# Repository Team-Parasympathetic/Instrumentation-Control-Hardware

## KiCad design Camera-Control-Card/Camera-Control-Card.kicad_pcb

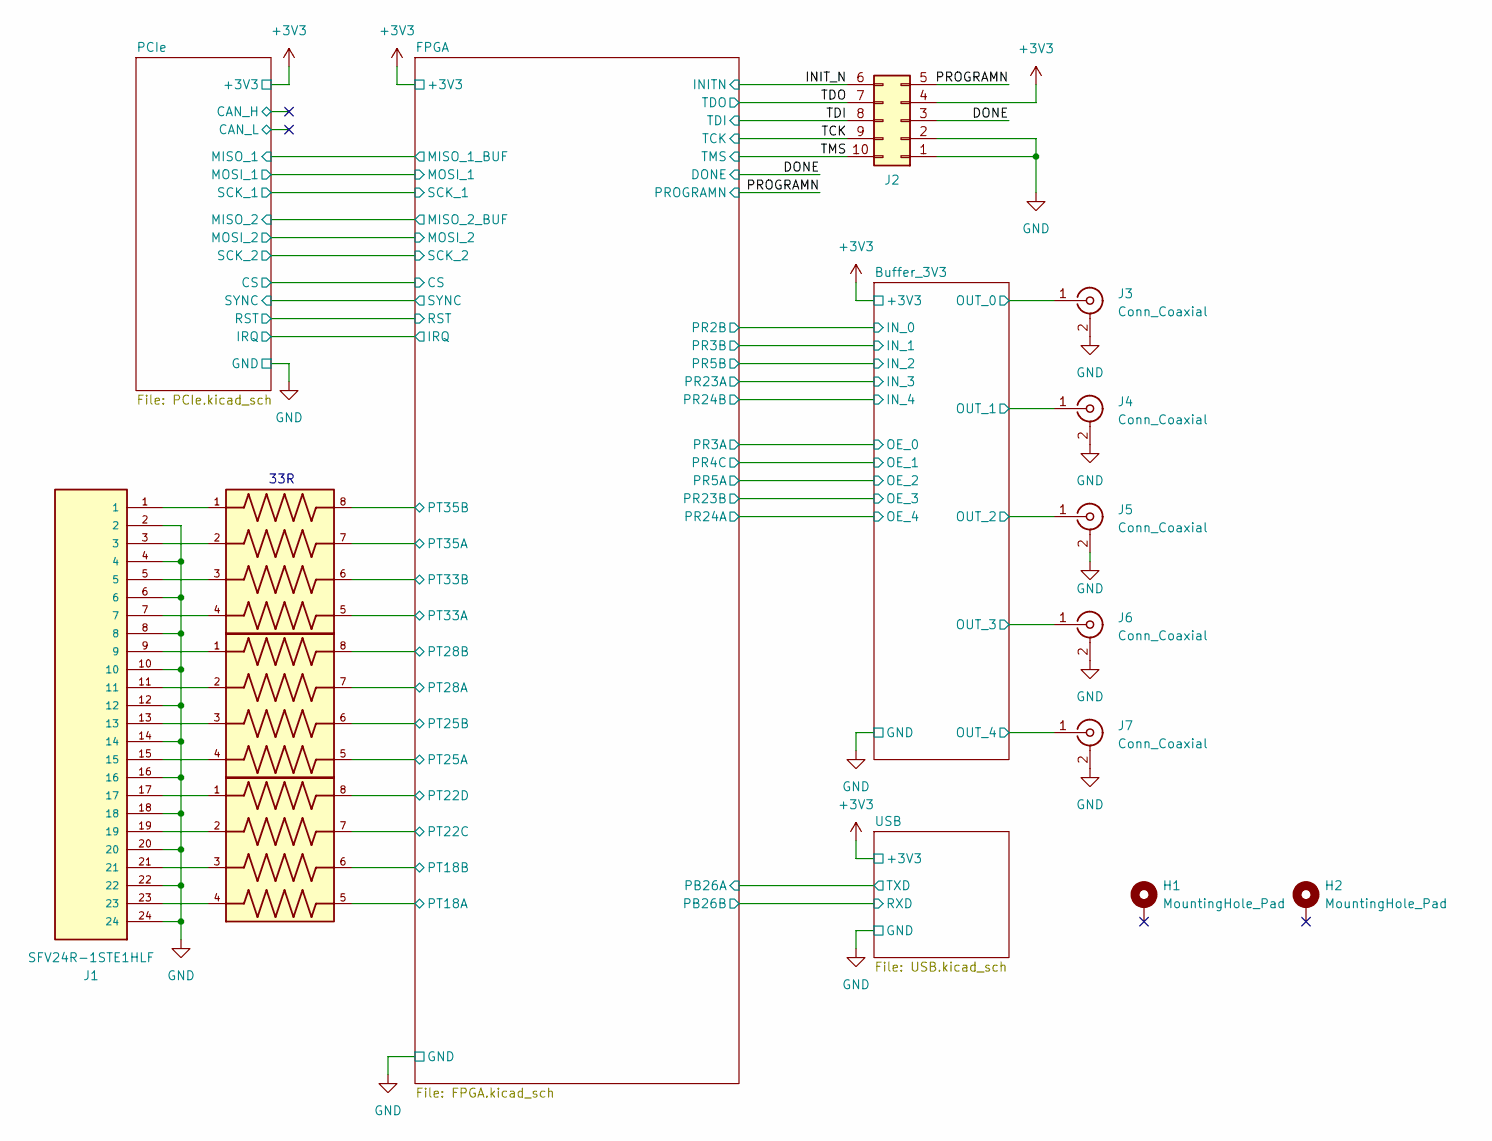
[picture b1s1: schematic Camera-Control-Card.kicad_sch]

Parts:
H1, H2: MountingHole_Pad; MountingHole_2.2mm_M2_DIN965_Pad_TopBottom
J1: SFV24R-1STE1HLF; AMPHENOL_SFV24R-1STE1HLF; PARTREV C
J2: Conn_02x05_Counter_Clockwise; AMPHENOL_78207-110HLF
J3, J4, J5, J6, J7: Conn_Coaxial; SMA_Molex_73251-1153_EdgeMount_Horizontal
RN1, RN2, RN3: EXB-38V330JV; RESCAXS80P320X160X60-8N

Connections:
+3V3: J2.4; also elsewhere on the board
/Buffer_3V3/OUT_0: J3.1 (In); also elsewhere on the board
/Buffer_3V3/OUT_1: J4.1 (In); also elsewhere on the board
/Buffer_3V3/OUT_2: J5.1 (In); also elsewhere on the board
/Buffer_3V3/OUT_3: J6.1 (In); also elsewhere on the board
/Buffer_3V3/OUT_4: J7.1 (In); also elsewhere on the board
/DONE: J2.3; also elsewhere on the board
/FPGA/PT18A: RN3.5; also elsewhere on the board
/FPGA/PT18B: RN3.6; also elsewhere on the board
/FPGA/PT22C: RN3.7; also elsewhere on the board
/FPGA/PT22D: RN3.8; also elsewhere on the board
/FPGA/PT25A: RN2.5; also elsewhere on the board
/FPGA/PT25B: RN2.6; also elsewhere on the board
/FPGA/PT28A: RN2.7; also elsewhere on the board
/FPGA/PT28B: RN2.8; also elsewhere on the board
/FPGA/PT33A: RN1.5; also elsewhere on the board
/FPGA/PT33B: RN1.6; also elsewhere on the board
/FPGA/PT35A: RN1.7; also elsewhere on the board
/FPGA/PT35B: RN1.8; also elsewhere on the board
/INIT_N: J2.6; also elsewhere on the board
/PROGRAMN: J2.5; also elsewhere on the board
/TCK: J2.9; also elsewhere on the board
/TDI: J2.8; also elsewhere on the board
/TDO: J2.7; also elsewhere on the board
/TMS: J2.10; also elsewhere on the board
GND: J1.2, J1.4, J1.6, J1.8, J1.10, J1.12, J1.14, J1.16, J1.18, J1.20, J1.22, J1.24, J2.1, J2.2, J3.2 (Ext), J4.2 (Ext), J5.2 (Ext), J6.2 (Ext), J7.2 (Ext); also elsewhere on the board
unnamed: J1.1, RN1.1
unnamed: J1.3, RN1.2
unnamed: J1.5, RN1.3
unnamed: J1.7, RN1.4
unnamed: J1.9, RN2.1
unnamed: J1.11, RN2.2
unnamed: J1.13, RN2.3
unnamed: J1.15, RN2.4
unnamed: J1.17, RN3.1
unnamed: J1.19, RN3.2
unnamed: J1.21, RN3.3
unnamed: J1.23, RN3.4

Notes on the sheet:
33R

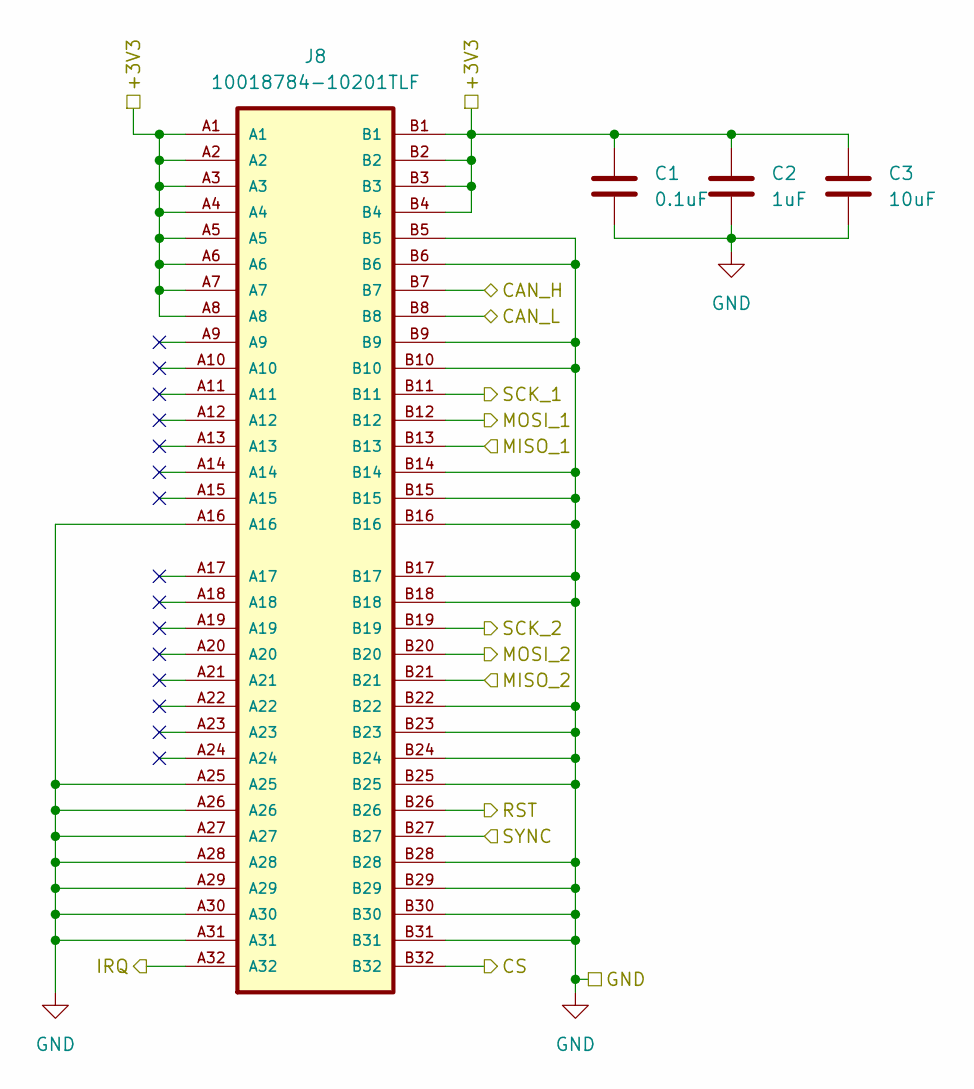
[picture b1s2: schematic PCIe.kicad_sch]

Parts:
C1: 0.1uF; C_0805_2012Metric
C2: 1uF; C_0805_2012Metric
C3: 10uF; CP_Elec_6.3x5.9
J8: 10018784-10201TLF; BUS_PCIexpress_x4; PARTREV A

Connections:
+3V3: C1.1, C2.1, C3.1, J8.A1, J8.A2, J8.A3, J8.A4, J8.A5, J8.A6, J8.A7, J8.A8, J8.B1, J8.B2, J8.B3, J8.B4; also elsewhere on the board
/FPGA/CS: J8.B32; also elsewhere on the board
/FPGA/IRQ: J8.A32; also elsewhere on the board
/FPGA/MISO_1_BUF: J8.B13; also elsewhere on the board
/FPGA/MISO_2_BUF: J8.B21; also elsewhere on the board
/FPGA/MOSI_1: J8.B12; also elsewhere on the board
/FPGA/MOSI_2: J8.B20; also elsewhere on the board
/FPGA/RST: J8.B26; also elsewhere on the board
/FPGA/SCK_1: J8.B11; also elsewhere on the board
/FPGA/SCK_2: J8.B19; also elsewhere on the board
/FPGA/SYNC: J8.B27; also elsewhere on the board
/PCIe/CAN_H: J8.B7
/PCIe/CAN_L: J8.B8
GND: C1.2, C2.2, C3.2, J8.A16, J8.A25, J8.A26, J8.A27, J8.A28, J8.A29, J8.A30, J8.A31, J8.B5, J8.B6, J8.B9, J8.B10, J8.B14, J8.B15, J8.B16, J8.B17, J8.B18, J8.B22, J8.B23, J8.B24, J8.B25, J8.B28, J8.B29, J8.B30, J8.B31; also elsewhere on the board

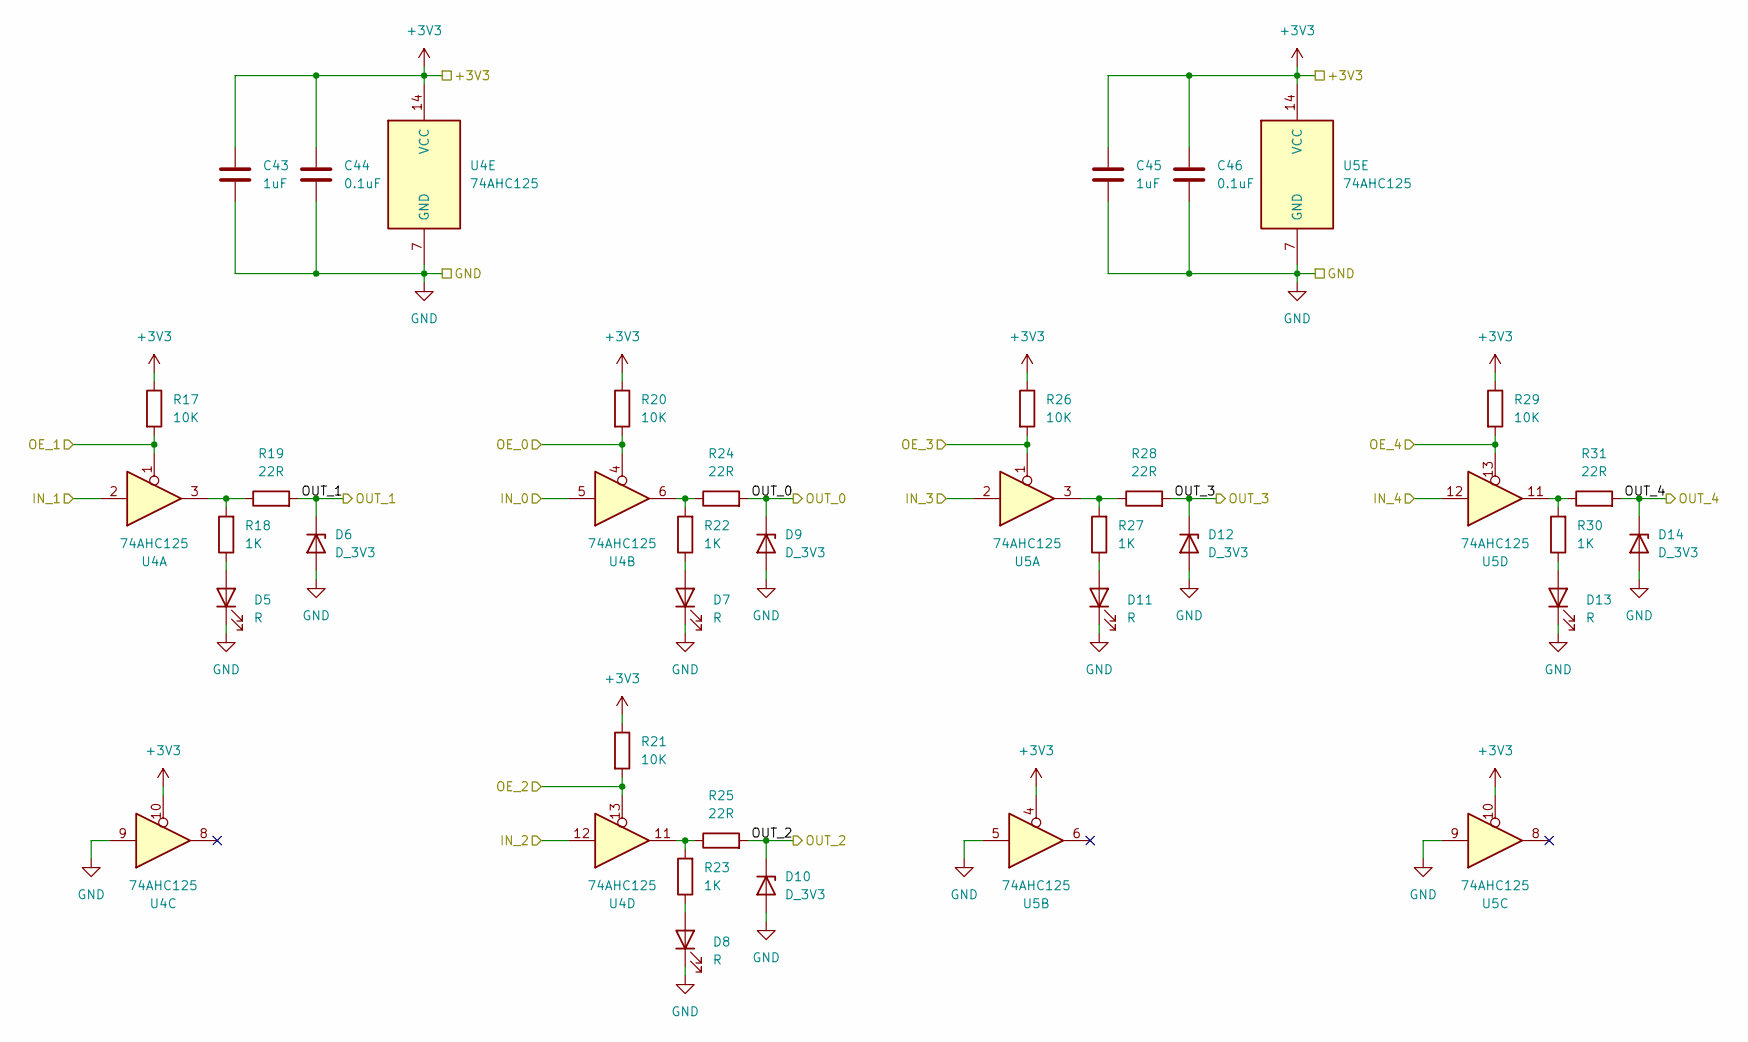
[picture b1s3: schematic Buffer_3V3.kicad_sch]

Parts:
C43, C45: 1uF; C_0603_1608Metric
C44, C46: 0.1uF; C_0603_1608Metric
D5, D7, D8, D11, D13: R; LED_0603_1608Metric
D6, D9, D10, D12, D14: D_3V3; D_SOD-323
R17, R20, R21, R26, R29: 10K; R_0603_1608Metric
R18, R22, R23, R27, R30: 1K; R_0603_1608Metric
R19, R24, R25, R28, R31: 22R; R_0603_1608Metric
U4, U5: 74AHC125; TSSOP-14_4.4x5mm_P0.65mm

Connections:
+3V3: C43.1, C44.1, C45.1, C46.1, R17.1, R20.1, R21.1, R26.1, R29.1, U4.10, U4.14 (VCC), U5.4, U5.10, U5.14 (VCC); also elsewhere on the board
/Buffer_3V3/IN_0: U4.5; also elsewhere on the board
/Buffer_3V3/IN_1: U4.2; also elsewhere on the board
/Buffer_3V3/IN_2: U4.12; also elsewhere on the board
/Buffer_3V3/IN_3: U5.2; also elsewhere on the board
/Buffer_3V3/IN_4: U5.12; also elsewhere on the board
/Buffer_3V3/OE_0: R20.2, U4.4; also elsewhere on the board
/Buffer_3V3/OE_1: R17.2, U4.1; also elsewhere on the board
/Buffer_3V3/OE_2: R21.2, U4.13; also elsewhere on the board
/Buffer_3V3/OE_3: R26.2, U5.1; also elsewhere on the board
/Buffer_3V3/OE_4: R29.2, U5.13; also elsewhere on the board
/Buffer_3V3/OUT_0: D9.1 (K), R24.2; also elsewhere on the board
/Buffer_3V3/OUT_1: D6.1 (K), R19.2; also elsewhere on the board
/Buffer_3V3/OUT_2: D10.1 (K), R25.2; also elsewhere on the board
/Buffer_3V3/OUT_3: D12.1 (K), R28.2; also elsewhere on the board
/Buffer_3V3/OUT_4: D14.1 (K), R31.2; also elsewhere on the board
GND: C43.2, C44.2, C45.2, C46.2, D5.1 (K), D6.2 (A), D7.1 (K), D8.1 (K), D9.2 (A), D10.2 (A), D11.1 (K), D12.2 (A), D13.1 (K), D14.2 (A), U4.7 (GND), U4.9, U5.5, U5.7 (GND), U5.9; also elsewhere on the board
unnamed: D5.2 (A), R18.1
unnamed: D7.2 (A), R22.1
unnamed: D8.2 (A), R23.1
unnamed: D11.2 (A), R27.1
unnamed: D13.2 (A), R30.1
unnamed: R18.2, R19.1, U4.3
unnamed: R22.2, R24.1, U4.6
unnamed: R23.2, R25.1, U4.11
unnamed: R27.2, R28.1, U5.3
unnamed: R30.2, R31.1, U5.11

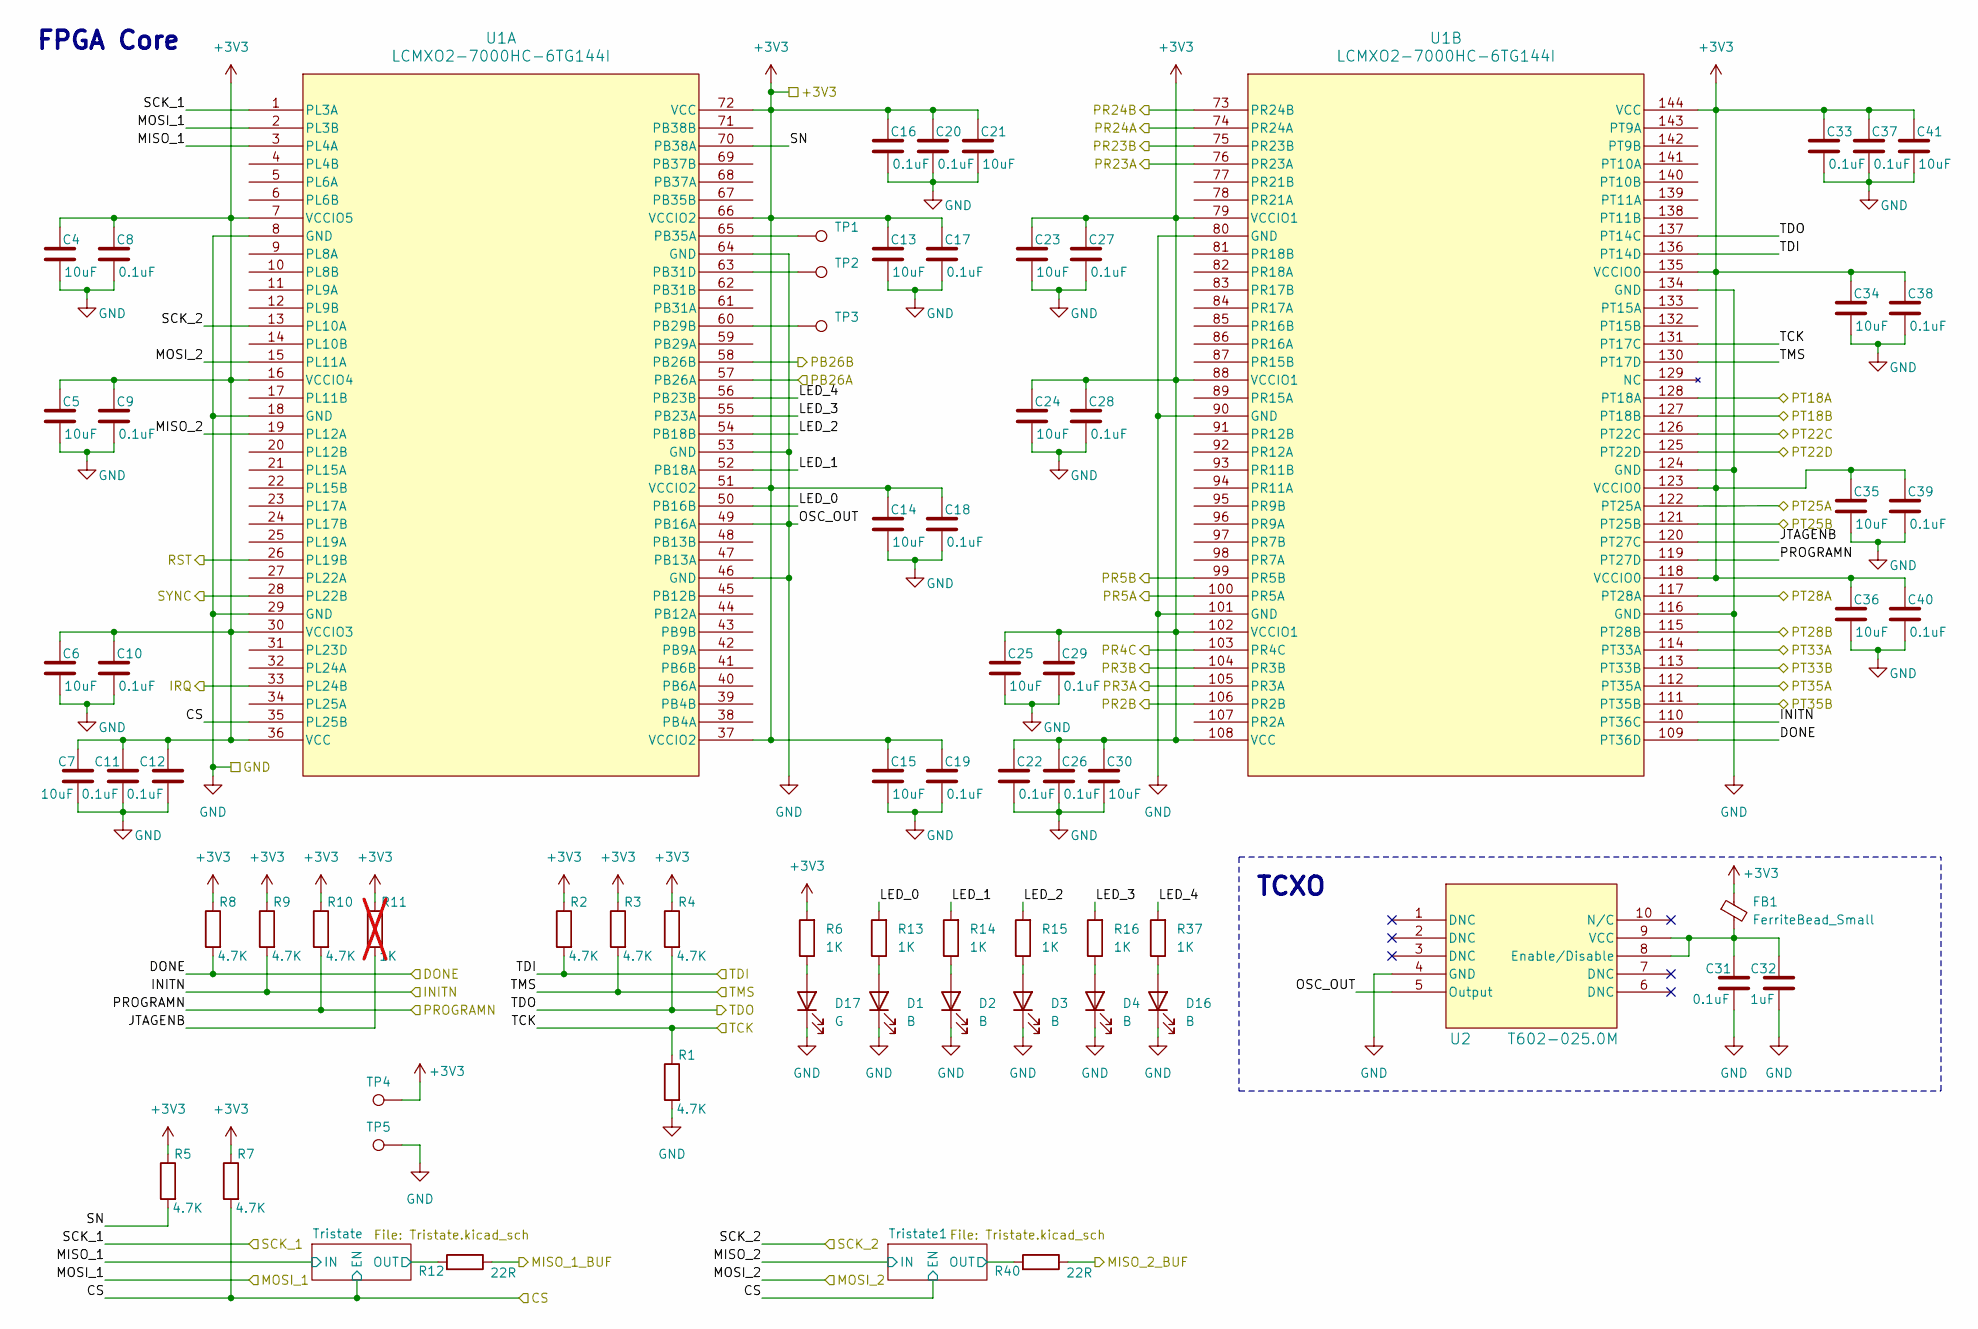
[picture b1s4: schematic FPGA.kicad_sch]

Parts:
C4, C5, C6, C7, C13, C14, C15, C21, C23, C24, C25, C30, C34, C35, C36, C41: 10uF; C_0603_1608Metric
C8, C9, C10, C11, C12, C16, C17, C18, C19, C20, C22, C26, C27, C28, C29, C31, C33, C37, C38, C39, C40: 0.1uF; C_0603_1608Metric
C32: 1uF; C_0603_1608Metric
D1, D2, D3, D4, D16: B; LED_0603_1608Metric
D17: G; LED_0603_1608Metric
FB1: FerriteBead_Small; L_0805_2012Metric
R1, R2, R3, R4, R5, R7, R8, R9, R10: 4.7K; R_0603_1608Metric
R6, R13, R14, R15, R16, R37: 1K; R_0603_1608Metric
R11: 1K; R_0603_1608Metric; not fitted
R12, R40: 22R; R_0603_1608Metric
TP1, TP2, TP3, TP4, TP5: TestPoint; TestPoint_Pad_D1.0mm
U1: LCMXO2-7000HC-6TG144I; TQFP144_LAT
U2: T602-025.0M; T602-025.0M_CNW

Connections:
+3V3: C4.1, C5.1, C6.1, C7.1, C8.1, C9.1, C10.1, C11.1, C12.1, C13.1, C14.1, C15.1, C16.1, C17.1, C18.1, C19.1, C20.1, C21.1, C22.1, C23.1, C24.1, C25.1, C26.1, C27.1, C28.1, C29.1, C30.1, C33.1, C34.1, C35.1, C36.1, C37.1, C38.1, C39.1, C40.1, C41.1, FB1.1, R2.1, R3.1, R4.1, R5.1, R6.2, R7.1, R8.1, R9.1, R10.1, R11.1, TP4.1, U1.7 (VCCIO5), U1.16 (VCCIO4), U1.30 (VCCIO3), U1.36 (VCC), U1.37 (VCCIO2), U1.51 (VCCIO2), U1.66 (VCCIO2), U1.72 (VCC), U1.79 (VCCIO1), U1.88 (VCCIO1), U1.102 (VCCIO1), U1.108 (VCC), U1.118 (VCCIO0), U1.123 (VCCIO0), U1.135 (VCCIO0), U1.144 (VCC); also elsewhere on the board
/Buffer_3V3/IN_0: U1.106 (PR2B); also elsewhere on the board
/Buffer_3V3/IN_1: U1.104 (PR3B); also elsewhere on the board
/Buffer_3V3/IN_2: U1.99 (PR5B); also elsewhere on the board
/Buffer_3V3/IN_3: U1.76 (PR23A); also elsewhere on the board
/Buffer_3V3/IN_4: U1.73 (PR24B); also elsewhere on the board
/Buffer_3V3/OE_0: U1.105 (PR3A); also elsewhere on the board
/Buffer_3V3/OE_1: U1.103 (PR4C); also elsewhere on the board
/Buffer_3V3/OE_2: U1.100 (PR5A); also elsewhere on the board
/Buffer_3V3/OE_3: U1.75 (PR23B); also elsewhere on the board
/Buffer_3V3/OE_4: U1.74 (PR24A); also elsewhere on the board
/DONE: R8.2, U1.109 (PT36D); also elsewhere on the board
/FPGA/CS: R7.2, U1.35 (PL25B); also elsewhere on the board
/FPGA/IRQ: U1.33 (PL24B); also elsewhere on the board
/FPGA/JTAGENB: R11.2, U1.120 (PT27C)
/FPGA/LED_0: R13.2, U1.50 (PB16B)
/FPGA/LED_1: R14.2, U1.52 (PB18A)
/FPGA/LED_2: R15.2, U1.54 (PB18B)
/FPGA/LED_3: R16.2, U1.55 (PB23A)
/FPGA/LED_4: R37.2, U1.56 (PB23B)
/FPGA/MISO_1: U1.3 (PL4A); also elsewhere on the board
/FPGA/MISO_1_BUF: R12.1; also elsewhere on the board
/FPGA/MISO_2: U1.19 (PL12A); also elsewhere on the board
/FPGA/MISO_2_BUF: R40.1; also elsewhere on the board
/FPGA/MOSI_1: U1.2 (PL3B); also elsewhere on the board
/FPGA/MOSI_2: U1.15 (PL11A); also elsewhere on the board
/FPGA/PB26A: U1.57 (PB26A); also elsewhere on the board
/FPGA/PB26B: U1.58 (PB26B); also elsewhere on the board
/FPGA/PT18A: U1.128 (PT18A); also elsewhere on the board
/FPGA/PT18B: U1.127 (PT18B); also elsewhere on the board
/FPGA/PT22C: U1.126 (PT22C); also elsewhere on the board
/FPGA/PT22D: U1.125 (PT22D); also elsewhere on the board
/FPGA/PT25A: U1.122 (PT25A); also elsewhere on the board
/FPGA/PT25B: U1.121 (PT25B); also elsewhere on the board
/FPGA/PT28A: U1.117 (PT28A); also elsewhere on the board
/FPGA/PT28B: U1.115 (PT28B); also elsewhere on the board
/FPGA/PT33A: U1.114 (PT33A); also elsewhere on the board
/FPGA/PT33B: U1.113 (PT33B); also elsewhere on the board
/FPGA/PT35A: U1.112 (PT35A); also elsewhere on the board
/FPGA/PT35B: U1.111 (PT35B); also elsewhere on the board
/FPGA/RST: U1.26 (PL19B); also elsewhere on the board
/FPGA/SCK_1: U1.1 (PL3A); also elsewhere on the board
/FPGA/SCK_2: U1.13 (PL10A); also elsewhere on the board
/FPGA/SN: R5.2, U1.70 (PB38A)
/FPGA/SYNC: U1.28 (PL22B); also elsewhere on the board
/FPGA/Tristate1/OUT: R40.2; also elsewhere on the board
/FPGA/Tristate/OUT: R12.2; also elsewhere on the board
/INIT_N: R9.2, U1.110 (PT36C); also elsewhere on the board
/PROGRAMN: R10.2, U1.119 (PT27D); also elsewhere on the board
/TCK: R1.1, U1.131 (PT17C); also elsewhere on the board
/TDI: R2.2, U1.136 (PT14D); also elsewhere on the board
/TDO: R4.2, U1.137 (PT14C); also elsewhere on the board
/TMS: R3.2, U1.130 (PT17D); also elsewhere on the board
GND: C4.2, C5.2, C6.2, C7.2, C8.2, C9.2, C10.2, C11.2, C12.2, C13.2, C14.2, C15.2, C16.2, C17.2, C18.2, C19.2, C20.2, C21.2, C22.2, C23.2, C24.2, C25.2, C26.2, C27.2, C28.2, C29.2, C30.2, C31.2, C32.2, C33.2, C34.2, C35.2, C36.2, C37.2, C38.2, C39.2, C40.2, C41.2, D1.1 (K), D2.1 (K), D3.1 (K), D4.1 (K), D16.1 (K), D17.1 (K), R1.2, TP5.1, U1.8 (GND), U1.18 (GND), U1.29 (GND), U1.46 (GND), U1.49 (PB16A), U1.53 (GND), U1.64 (GND), U1.80 (GND), U1.90 (GND), U1.101 (GND), U1.116 (GND), U1.124 (GND), U1.134 (GND), U2.4 (GND), U2.5 (Output); also elsewhere on the board
unnamed: D1.2 (A), R13.1
unnamed: D2.2 (A), R14.1
unnamed: D3.2 (A), R15.1
unnamed: D4.2 (A), R16.1
unnamed: D16.2 (A), R37.1
unnamed: D17.2 (A), R6.1
unnamed: TP3.1, U1.60 (PB29B)
unnamed: TP2.1, U1.63 (PB31D)
unnamed: TP1.1, U1.65 (PB35A)
unnamed: C31.1, C32.1, FB1.2, U2.8 (Enable/Disable), U2.9 (VCC)

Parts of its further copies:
C52: 0.1uF; C_0603_1608Metric

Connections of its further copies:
+3V3: C52.1; also elsewhere on the board
GND: C52.2; also elsewhere on the board

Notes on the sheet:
TCXO
FPGA Core

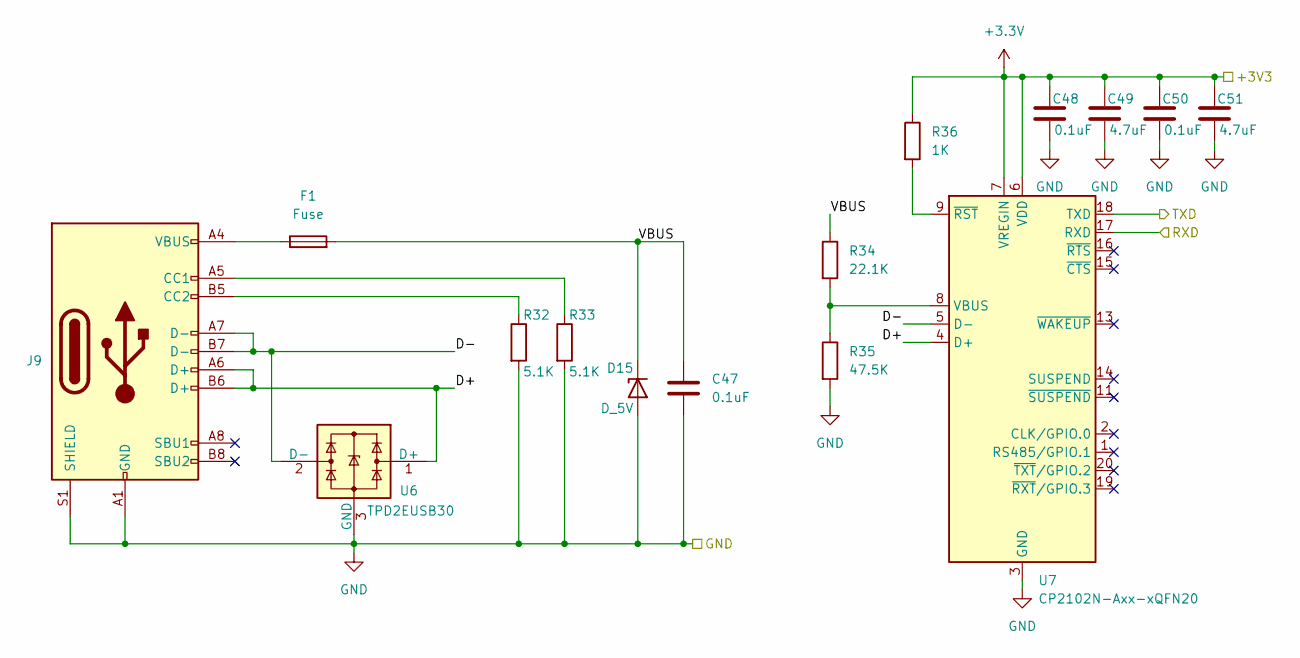
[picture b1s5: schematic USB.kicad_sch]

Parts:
C47, C48, C50: 0.1uF; C_0603_1608Metric
C49, C51: 4.7uF; C_0603_1608Metric
D15: D_5V; D_SOD-323
F1: Fuse; Fuse_0603_1608Metric
J9: USB_C_Receptacle_USB2.0_16P; USB_C_Receptacle_G-Switch_GT-USB-7010ASV
R32, R33: 5.1K; R_0603_1608Metric
R34: 22.1K; R_0603_1608Metric
R35: 47.5K; R_0603_1608Metric
R36: 1K; R_0603_1608Metric
U6: TPD2EUSB30; Texas_DRT-3
U7: CP2102N-Axx-xQFN20; SiliconLabs_QFN-20-1EP_3x3mm_P0.5mm_EP1.8x1.8mm

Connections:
+3V3: C48.1, C49.1, C50.1, C51.1, R36.1, U7.6 (VDD), U7.7 (VREGIN); also elsewhere on the board
/FPGA/PB26A: U7.18 (TXD); also elsewhere on the board
/FPGA/PB26B: U7.17 (RXD); also elsewhere on the board
/USB/D+: J9.A6 (D+), J9.B6 (D+), U6.1 (D+), U7.4 (D+)
/USB/D-: J9.A7 (D-), J9.B7 (D-), U6.2 (D-), U7.5 (D-)
/USB/VBUS: C47.1, D15.1 (K), F1.2, R34.1
GND: C47.2, C48.2, C49.2, C50.2, C51.2, D15.2 (A), J9.A1 (GND), J9.A12 (GND), J9.B1 (GND), J9.B12 (GND), J9.S1 (SHIELD), R32.2, R33.2, R35.2, U6.3 (GND), U7.3 (GND), U7.12 (GND), U7.21 (GND); also elsewhere on the board
unnamed: F1.1, J9.A4 (VBUS), J9.A9 (VBUS), J9.B4 (VBUS), J9.B9 (VBUS)
unnamed: J9.A5 (CC1), R33.1
unnamed: J9.B5 (CC2), R32.1
unnamed: R34.2, R35.1, U7.8 (VBUS)
unnamed: R36.2, U7.9 (~RST)

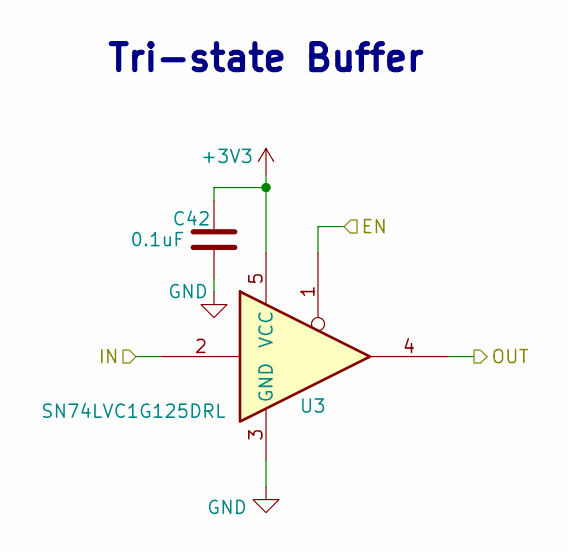
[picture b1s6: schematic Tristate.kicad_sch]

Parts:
C42: 0.1uF; C_0603_1608Metric
U3: SN74LVC1G125DRL; Texas_R-PDSO-N5_DRL-5

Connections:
+3V3: C42.1, U3.5 (VCC); also elsewhere on the board
/FPGA/CS: U3.1; also elsewhere on the board
/FPGA/MISO_1: U3.2; also elsewhere on the board
/FPGA/Tristate/OUT: U3.4; also elsewhere on the board
GND: C42.2, U3.3 (GND); also elsewhere on the board

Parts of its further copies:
C52: 0.1uF; C_0603_1608Metric
U8: SN74LVC1G125DRL; Texas_R-PDSO-N5_DRL-5

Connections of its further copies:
+3V3: C52.1, U8.5 (VCC); also elsewhere on the board
/FPGA/CS: U8.1; also elsewhere on the board
/FPGA/MISO_2: U8.2; also elsewhere on the board
/FPGA/Tristate1/OUT: U8.4; also elsewhere on the board
GND: C52.2, U8.3 (GND); also elsewhere on the board

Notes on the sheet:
Tri-state Buffer

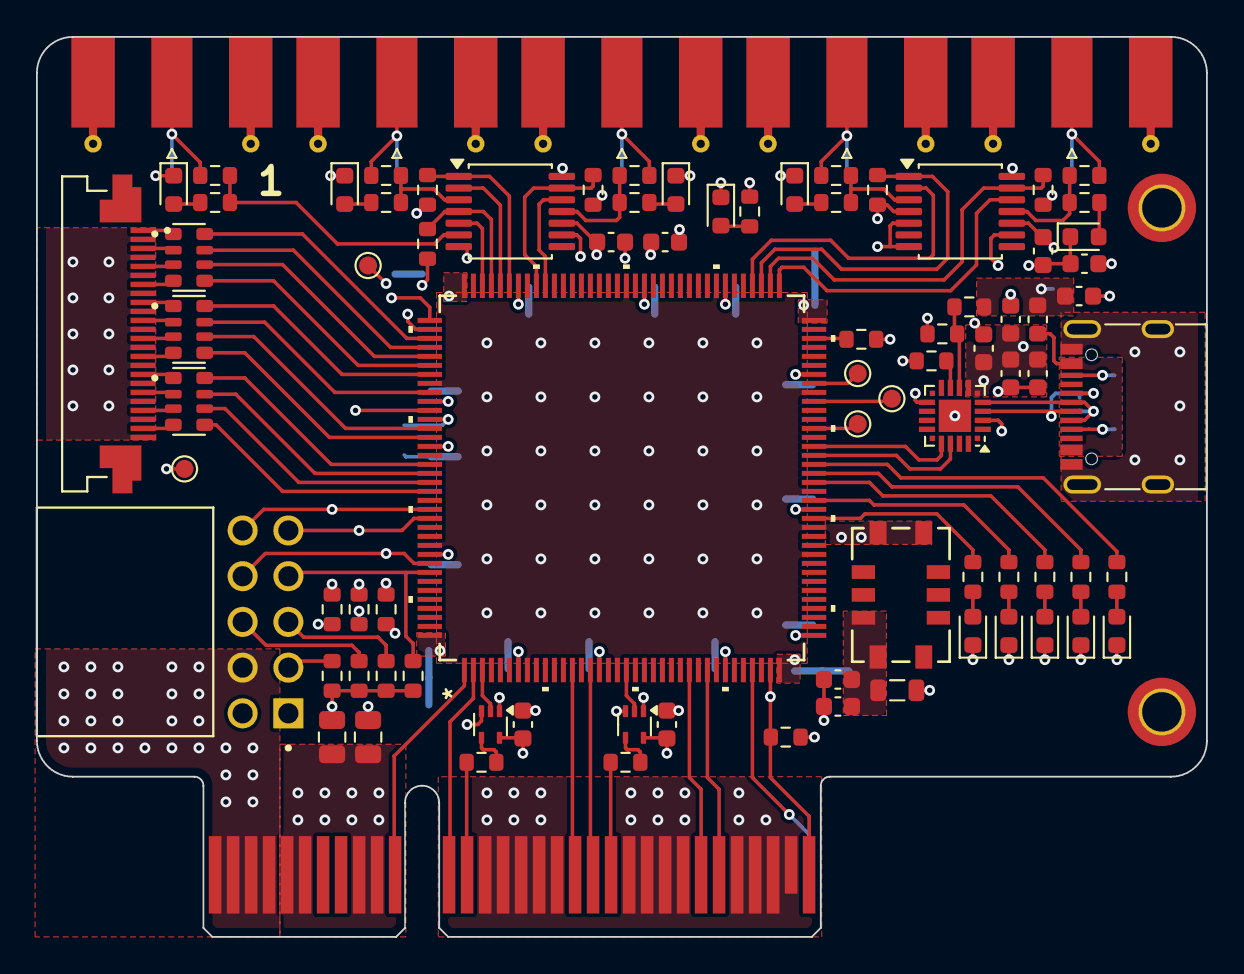
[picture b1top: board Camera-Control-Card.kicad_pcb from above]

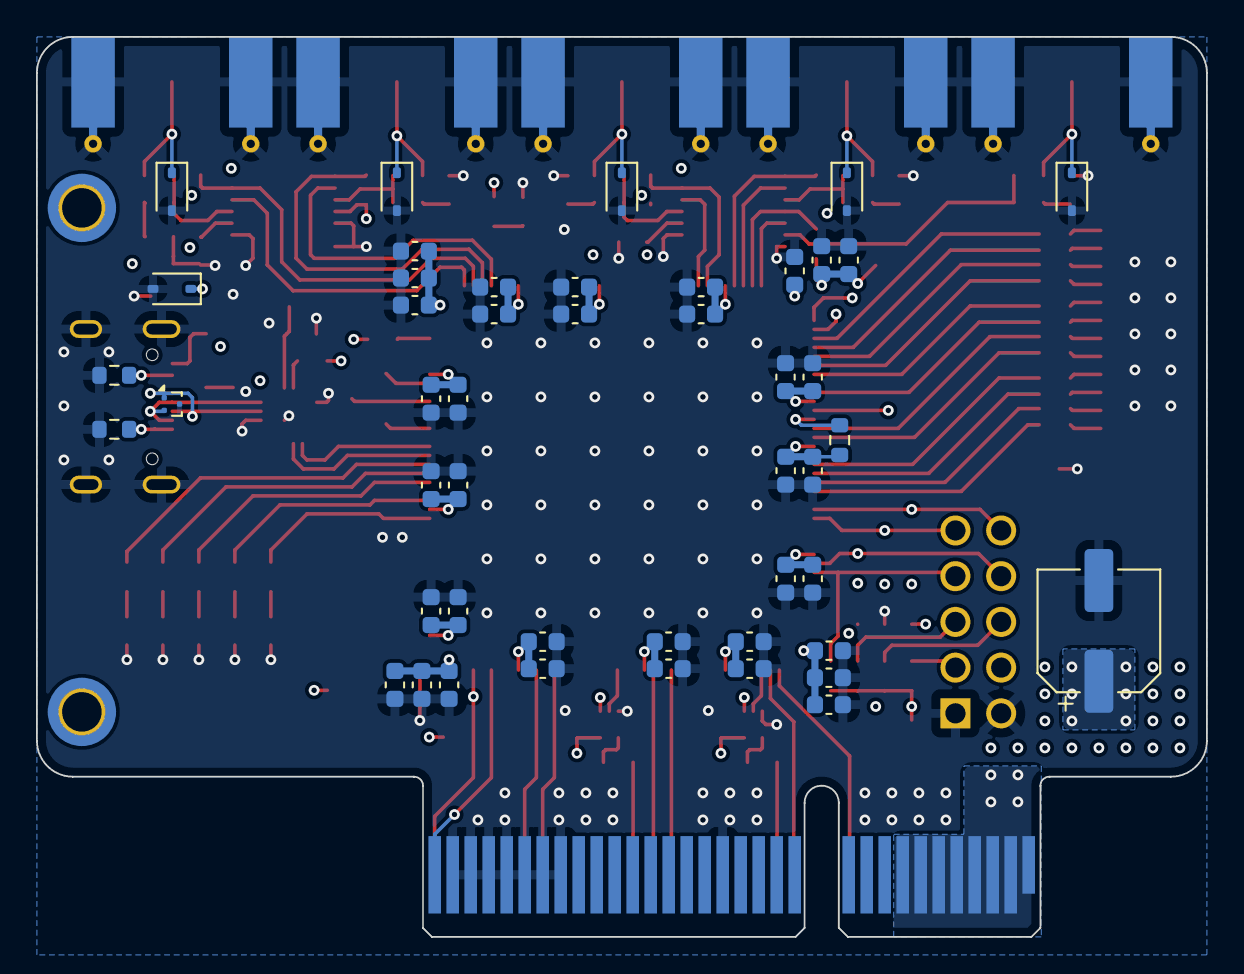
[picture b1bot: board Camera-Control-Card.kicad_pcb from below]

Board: 4 copper layers, 65.0 x 50.0 mm, 136 parts (47 on the bottom side), 99 nets.
